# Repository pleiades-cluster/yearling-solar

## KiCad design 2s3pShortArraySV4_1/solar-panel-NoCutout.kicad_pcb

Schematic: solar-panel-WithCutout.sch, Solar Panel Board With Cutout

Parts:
D1, D2, D3: CDBA240LL-HF; DO-214AC
J1: CON-5040500591; CON_5040500591
J2, J3, J4, J5: Conn_01x01; MountingHoles
SC1, SC2, SC3, SC4, SC5, SC6: SM101K07TF
U1: APDS9960_Breakout; APDS9960
U2: BNO080_Breakout; BNO080
U3: MCP9808_Breakout; MCP9808

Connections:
+3V3: J1.3, U1.1 (VDD), U2.1, U3.1
GND: J1.2, SC2.2, SC4.2, SC6.2, U1.3 (GND), U2.2, U3.2
unnamed: D1.2, SC1.1
unnamed: D2.2, SC3.1
unnamed: D3.2, SC5.1
unnamed: SC1.2, SC2.1
unnamed: SC3.2, SC4.1
unnamed: SC5.2, SC6.1
unnamed: U2.6, U2.7
SCL: J1.4, U1.4 (SCL), U2.3, U3.3
SDA: J1.5, U1.5 (SDA), U2.4, U3.4
VSOLAR: D1.1, D2.1, D3.1, J1.1

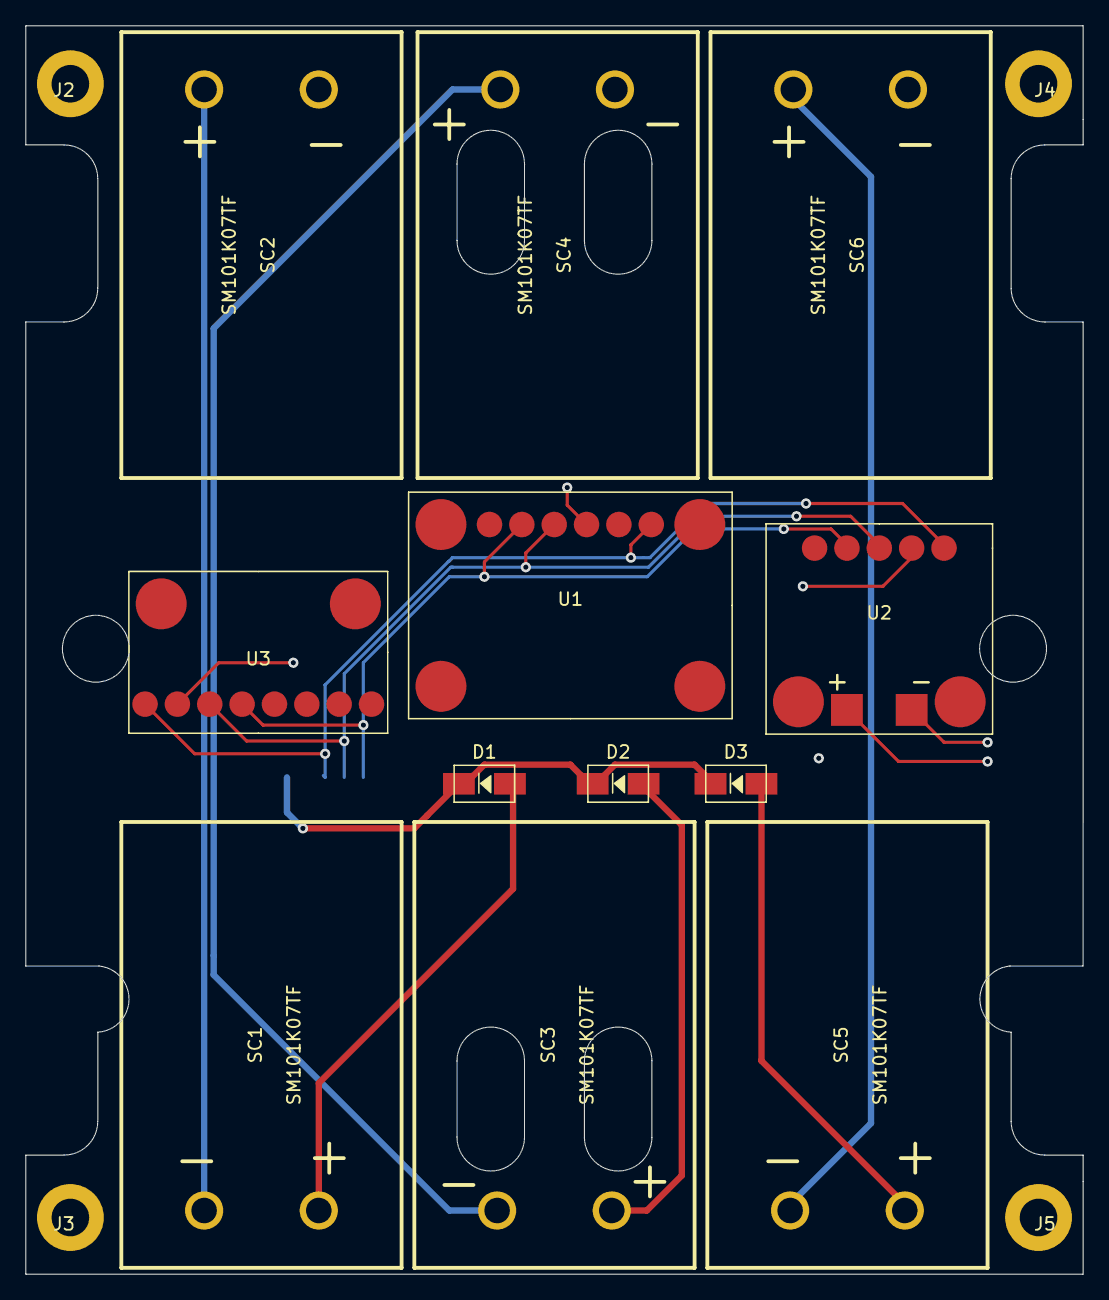
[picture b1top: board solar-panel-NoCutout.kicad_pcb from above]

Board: 4 copper layers, 83.0 x 98.0 mm, 17 parts (1 on the bottom side), 12 nets.

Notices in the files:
parts and their libraries:
Copyright 2021 Accelerated Designs. All rights reserved.
